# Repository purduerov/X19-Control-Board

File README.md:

# X19 Control Board

Primary microcontroller board managing actuator actuation, telemetry collection, and vehicle subsystem communication for the Purdue ROV X19 vehicle.

---

## 🚀 Quickstart: Opening the Project (Recommended)

**Always open the project using the 1-click launcher:**

* **Windows:** Double-click `LAUNCH_KICAD.bat`
* **macOS / Linux:** Run `./LAUNCH_KICAD.sh`

### What the Launcher Does Automatically:
1. ⚙️ **Configures Git Hooks & Clean Filters:** Sets up Git to strip volatile viewport/zoom coordinates on every commit, preventing merge conflicts.
2. 🔄 **Auto-Updates Component Library:** Pulls the freshest symbols, footprints, and 3D models from `purdue-rov-kicad-lib` before opening.
3. 📐 **Opens KiCad:** Launches `X19-Control-Board.kicad_pro` with all 6 central library categories pre-linked.

---

## Cloning the Repository
Clone recursively to ensure the central component library is initialized:
```bash
git clone --recursive https://github.com/purduerov/X19-Control-Board.git
cd X19-Control-Board
```

## Central Component Library & Manager GUI

The project links to the central `purdue-rov-kicad-lib` submodule mapped across 6 categories in `sym-lib-table` and `fp-lib-table`:
- `rov_passives`: Resistors, capacitors, inductors, crystals
- `rov_power`: Voltage regulators, buck/boost converters, MOSFETs, diodes
- `rov_logic`: MCUs, logic ICs, op-amps, drivers, level shifters
- `rov_connectors`: Power terminals, XT60, headers, USB, JST connectors
- `rov_sensors`: IMUs, temperature, pressure sensors
- `rov_mech`: Mounting holes, standoffs, test points

### Launching the Library Manager GUI
To browse parts, inspect footprints, edit properties, or add/delete components in the shared library:
- **Windows:** Double-click `libs\purdue-rov-kicad-lib\LIBRARY_MANAGER.bat`
- **macOS / Linux:** Run `./libs/purdue-rov-kicad-lib/LIBRARY_MANAGER.sh`

## Design Rules & Clearances

- Clearance constraints (JLCPCB 4-layer rules) are configured in `X19-Control-Board.kicad_dru`.
- All symbols and footprints must comply with central library guidelines.

## Automated CI/CD & DevOps Preflight Checks

All CI/CD automation and tooling are centralized in [`purduerov/pcb-devops`](https://github.com/purduerov/pcb-devops):
1. **Automated Git Clean Filters:** Configured automatically by `.githooks/pre-commit` to prevent viewport/zoom merge noise.
2. **KiCad Symbol Linting:** Validates mandatory fields (`MPN`, `Manufacturer`, `Category`, `DigiKey`, `Datasheet`, `Temp_Range`) on all library components.
3. **ERC & DRC Validation:** Executes Electrical and Design Rules Checks via KiBot in GitHub Actions.
4. **Artifact Generation:** Automatically exports Schematic PDFs, Board Layout PDFs, and Interactive HTML BOMs on every pull request.

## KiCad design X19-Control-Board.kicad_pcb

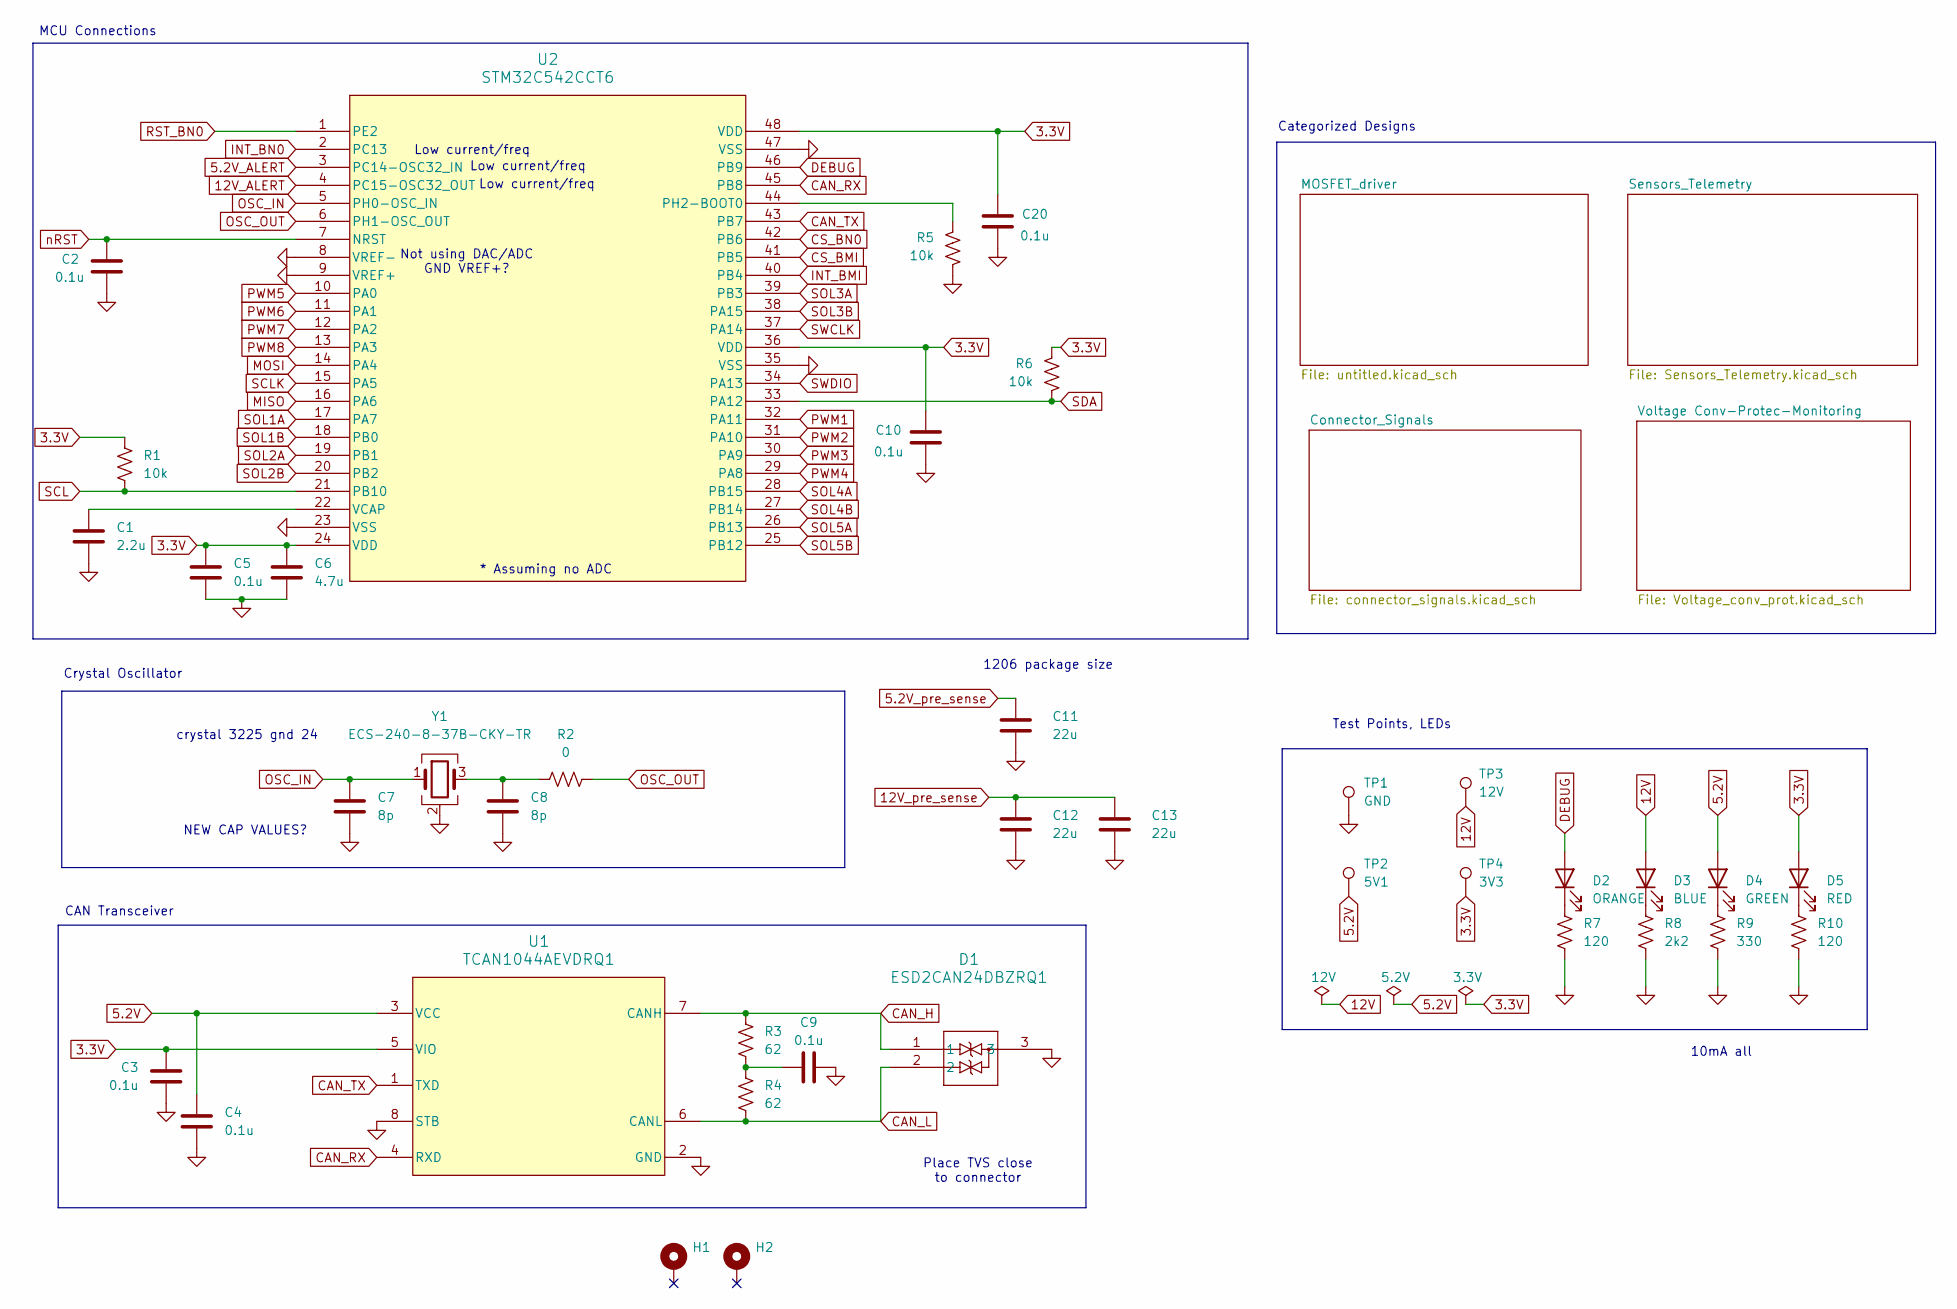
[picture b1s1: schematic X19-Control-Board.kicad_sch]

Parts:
C1: 2.2u; C_0603_1608Metric_Pad1.08x0.95mm_HandSolder; Part Number CC0603KRX5R6BB225
C2, C3, C4, C5, C9, C10, C20: 0.1u; C_0603_1608Metric_Pad1.08x0.95mm_HandSolder; Part Number CC0603KRX7R8BB104
C6: 4.7u; C_0603_1608Metric_Pad1.08x0.95mm_HandSolder; Part Number CC0603KRX5R6BB475
C7, C8: 8p; C_0603_1608Metric_Pad1.08x0.95mm_HandSolder; Part Number CC0603DRNPO9BN8R0
C11, C12, C13: 22u; C_1206_3216Metric_Pad1.33x1.80mm_HandSolder; Part Number CC1206KKX5R8BB226
D1: ESD2CAN24DBZRQ1; SOT-23-3; Part Number ESD2CAN24DBZRQ1
D2: ORANGE; LED_0603_1608Metric; Part Number LTST-C190AKT
D3: BLUE; LED_0603_1608Metric; Part Number LTST-C190TBKT
D4: GREEN; LED_0603_1608Metric; Part Number LTST-C190GKT
D5: RED; LED_0603_1608Metric; Part Number LTST-C190KRKT
H1, H2: MountingHole_Pad; MountingHole_2.7mm_M2.5_Pad
R1, R5, R6: 10k; R_0603_1608Metric_Pad0.98x0.95mm_HandSolder; Part Number RC0603FR-0710KL
R2: 0; R_0603_1608Metric_Pad0.98x0.95mm_HandSolder; Part Number RC0603FR-070RL
R3, R4: 62; R_0603_1608Metric_Pad0.98x0.95mm_HandSolder; Part Number RC0603FR-0762RL
R7, R10: 120; R_0603_1608Metric_Pad0.98x0.95mm_HandSolder; Part Number RC0603FR-07120RL
R8: 2k2; R_0603_1608Metric_Pad0.98x0.95mm_HandSolder; Part Number RC0603FR-072K2L
R9: 330; R_0603_1608Metric_Pad0.98x0.95mm_HandSolder; Part Number RC0603FR-07330RL
TP1: GND; TestPoint_Pad_D1.5mm
TP2: 5V1; TestPoint_Pad_D1.5mm
TP3: 12V; TestPoint_Pad_D1.5mm
TP4: 3V3; TestPoint_Pad_D1.5mm
U1: TCAN1044AEVDRQ1; SOIC-8_3.9x4.9mm_P1.27mm; Part Number TCAN1044AEVDRQ1
U2: STM32C542CCT6; LQFP-48_7x7mm_P0.5mm; Part Number STM32C542CCT6
Y1: ECS-240-8-37B-CKY-TR; Crystal_SMD_2016-4Pin_2.0x1.6mm; Part Number ECS-240-8-37B-CKY-TR

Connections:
3.3V: C3.1, C5.1, C6.1, C10.2, C20.2, D5.2 (A), R1.1, R6.1, TP4.1 (1_1), U1.5 (VIO), U2.24 (VDD), U2.36 (VDD), U2.48 (VDD); also elsewhere on the board
5.2V: C4.1, D4.2 (A), TP2.1 (1_1), U1.3 (VCC); also elsewhere on the board
5.2V_ALERT: U2.3 (PC14-OSC32_IN); also elsewhere on the board
5.2V_pre_sense: C11.1; also elsewhere on the board
12V: D3.2 (A), TP3.1 (1_1); also elsewhere on the board
12V_ALERT: U2.4 (PC15-OSC32_OUT); also elsewhere on the board
12V_pre_sense: C12.1, C13.1; also elsewhere on the board
CAN_H: D1.1, R3.1, U1.7 (CANH); also elsewhere on the board
CAN_L: D1.2, R4.2, U1.6 (CANL); also elsewhere on the board
CAN_RX: U1.4 (RXD), U2.45 (PB8)
CAN_TX: U1.1 (TXD), U2.43 (PB7)
CS_BMI: U2.41 (PB5); also elsewhere on the board
CS_BN0: U2.42 (PB6); also elsewhere on the board
DEBUG: D2.2 (A), U2.46 (PB9)
GND: C1.2, C2.1, C3.2, C4.2, C5.2, C6.2, C7.2, C8.2, C9.2, C10.1, C11.2, C12.2, C13.2, C20.1, D1.3, R5.2, R7.2, R8.2, R9.2, R10.2, TP1.1 (1_1), U1.2 (GND), U1.8 (STB), U2.8 (VREF-), U2.9 (VREF+), U2.23 (VSS), U2.35 (VSS), U2.47 (VSS), Y1.2 (G), Y1.4 (G); also elsewhere on the board
INT_BMI: U2.40 (PB4); also elsewhere on the board
INT_BN0: U2.2 (PC13); also elsewhere on the board
MISO: U2.16 (PA6); also elsewhere on the board
MOSI: U2.14 (PA4); also elsewhere on the board
unnamed: C8.1, R2.1, Y1.3
unnamed: C9.1, R3.2, R4.1
unnamed: D2.1 (K), R7.1
unnamed: D3.1 (K), R8.1
unnamed: D4.1 (K), R9.1
unnamed: D5.1 (K), R10.1
unnamed: R5.1, U2.44 (PH2-BOOT0)
unnamed: C1.1, U2.22 (VCAP)
OSC_IN: C7.1, U2.5 (PH0-OSC_IN), Y1.1
OSC_OUT: R2.2, U2.6 (PH1-OSC_OUT)
PWM1: U2.32 (PA11); also elsewhere on the board
PWM2: U2.31 (PA10); also elsewhere on the board
PWM3: U2.30 (PA9); also elsewhere on the board
PWM4: U2.29 (PA8); also elsewhere on the board
PWM5: U2.10 (PA0); also elsewhere on the board
PWM6: U2.11 (PA1); also elsewhere on the board
PWM7: U2.12 (PA2); also elsewhere on the board
PWM8: U2.13 (PA3); also elsewhere on the board
RST_BN0: U2.1 (PE2); also elsewhere on the board
SCL: R1.2, U2.21 (PB10); also elsewhere on the board
SCLK: U2.15 (PA5); also elsewhere on the board
SDA: R6.2, U2.33 (PA12); also elsewhere on the board
SOL1A: U2.17 (PA7); also elsewhere on the board
SOL1B: U2.18 (PB0); also elsewhere on the board
SOL2A: U2.19 (PB1); also elsewhere on the board
SOL2B: U2.20 (PB2); also elsewhere on the board
SOL3A: U2.39 (PB3); also elsewhere on the board
SOL3B: U2.38 (PA15); also elsewhere on the board
SOL4A: U2.28 (PB15); also elsewhere on the board
SOL4B: U2.27 (PB14); also elsewhere on the board
SOL5A: U2.26 (PB13); also elsewhere on the board
SOL5B: U2.25 (PB12); also elsewhere on the board
SWCLK: U2.37 (PA14); also elsewhere on the board
SWDIO: U2.34 (PA13); also elsewhere on the board
nRST: C2.2, U2.7 (NRST); also elsewhere on the board

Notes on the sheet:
Test Points, LEDs
Low current/freq
CAN Transceiver
* Assuming no ADC
1206 package size
Crystal Oscillator
Not using DAC/ADC GND VREF+?
NEW CAP VALUES?
MCU Connections
10mA all
crystal 3225 gnd 24
Place TVS close to connector
Categorized Designs

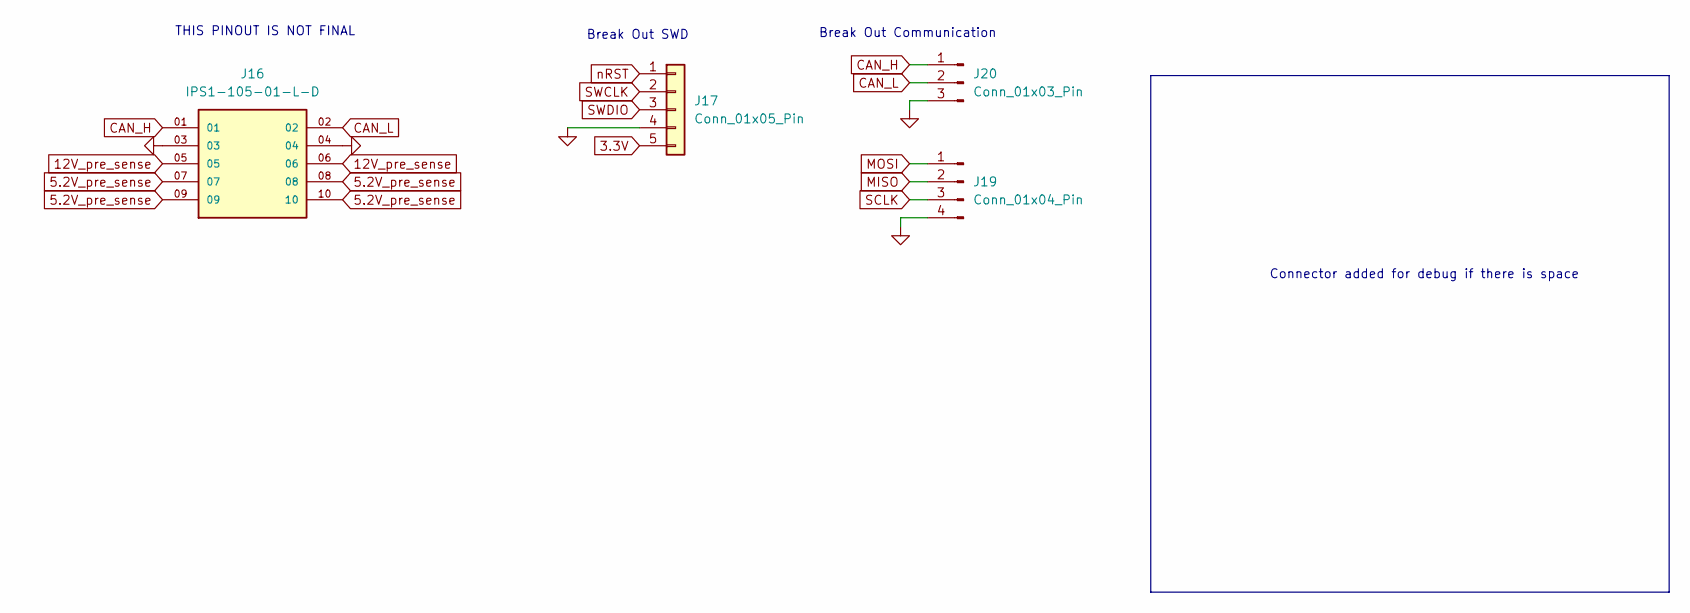
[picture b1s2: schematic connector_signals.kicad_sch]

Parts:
J16: IPS1-105-01-L-D; SAMTEC_IPS1-105-01-S-D; PARTREV R
J17: Conn_01x05_Pin; PinHeader_1x05_P2.54mm_Vertical; Part Number Generic
J19: Conn_01x04_Pin; PinHeader_1x04_P2.54mm_Vertical; Part Number Generic
J20: Conn_01x03_Pin; PinHeader_1x03_P2.54mm_Vertical; Part Number Generic

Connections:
3.3V: J17.5; also elsewhere on the board
5.2V_pre_sense: J16.07, J16.08, J16.09, J16.10; also elsewhere on the board
12V_pre_sense: J16.05, J16.06; also elsewhere on the board
CAN_H: J16.01, J20.1; also elsewhere on the board
CAN_L: J16.02, J20.2; also elsewhere on the board
GND: J16.03, J16.04, J17.4, J19.4, J20.3; also elsewhere on the board
MISO: J19.2; also elsewhere on the board
MOSI: J19.1; also elsewhere on the board
SCLK: J19.3; also elsewhere on the board
SWCLK: J17.2; also elsewhere on the board
SWDIO: J17.3; also elsewhere on the board
nRST: J17.1; also elsewhere on the board

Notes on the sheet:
Break Out Communication
Connector added for debug if there is space
THIS PINOUT IS NOT FINAL
Break Out SWD

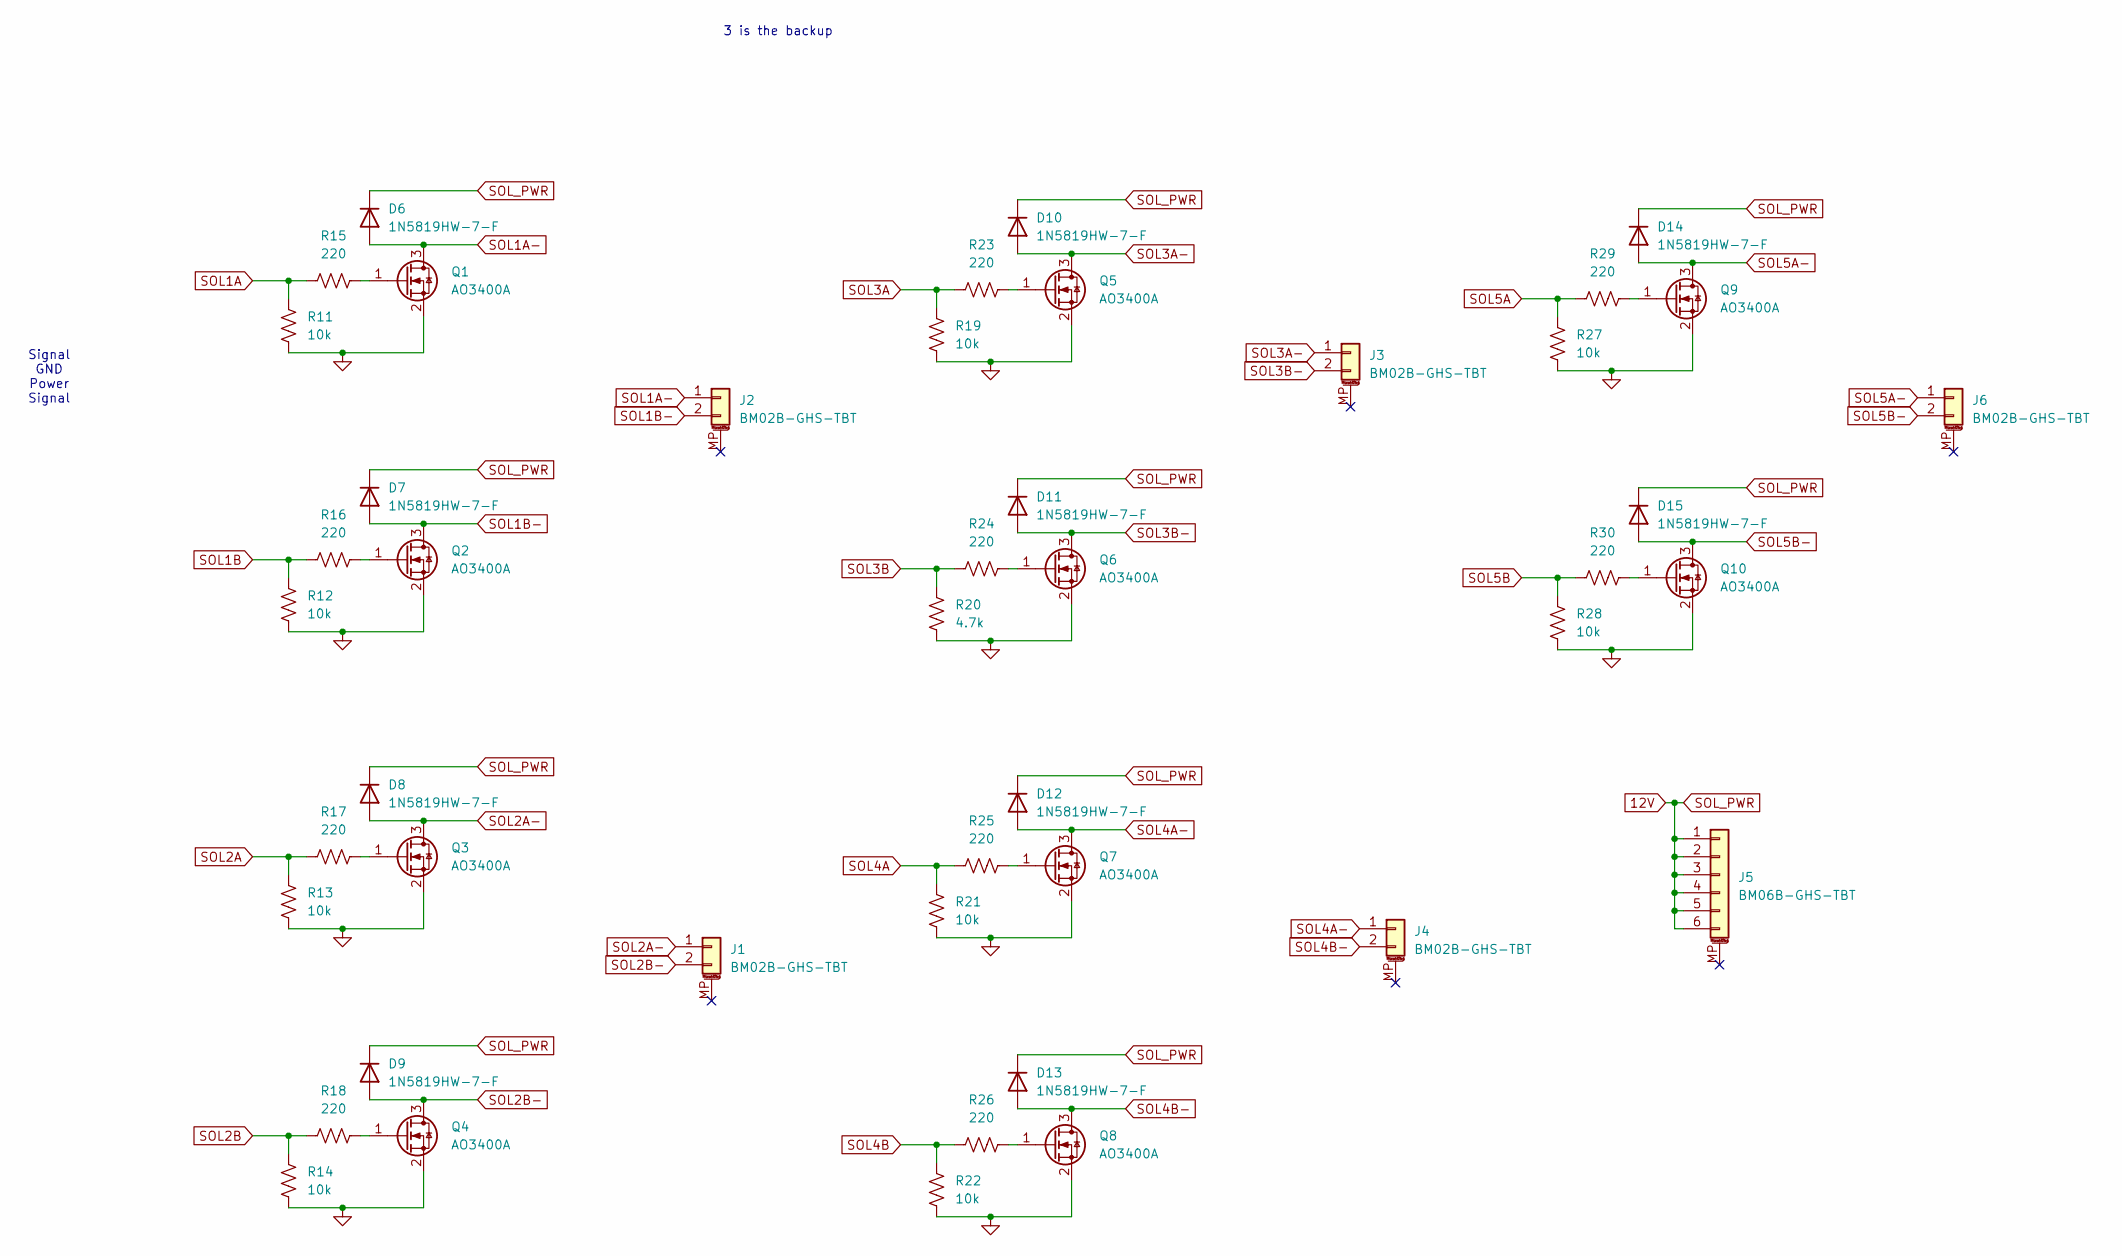
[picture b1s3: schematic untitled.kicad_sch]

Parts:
D6, D7, D8, D9, D10, D11, D12, D13, D14, D15: 1N5819HW-7-F; D_SOD-123; Part Number 1N5819HW-7-F
J1, J2, J3, J4, J6: BM02B-GHS-TBT; JST_GH_BM02B-GHS-TBT_1x02-1MP_P1.25mm_Vertical; Part Number BM02B-GHS-TBT
J5: BM06B-GHS-TBT; JST_GH_BM06B-GHS-TBT_1x06-1MP_P1.25mm_Vertical; Part Number BM06B-GHS-TBT
Q1, Q2, Q3, Q4, Q5, Q6, Q7, Q8, Q9, Q10: AO3400A; SOT-23-3; Part Number AO3400A
R11, R12, R13, R14, R19, R21, R22, R27, R28: 10k; R_0603_1608Metric_Pad0.98x0.95mm_HandSolder; Part Number RC0603FR-0710KL
R15, R16, R17, R18, R23, R24, R25, R26, R29, R30: 220; R_0603_1608Metric_Pad0.98x0.95mm_HandSolder; Part Number RC0603FR-07220RL
R20: 4.7k; R_0603_1608Metric_Pad0.98x0.95mm_HandSolder; Part Number RC0603FR-074K7L

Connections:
12V: D6.1 (K), D7.1 (K), D8.1 (K), D9.1 (K), D10.1 (K), D11.1 (K), D12.1 (K), D13.1 (K), D14.1 (K), D15.1 (K), J5.1, J5.2, J5.3, J5.4, J5.5, J5.6; also elsewhere on the board
GND: Q1.2 (S), Q2.2 (S), Q3.2 (S), Q4.2 (S), Q5.2 (S), Q6.2 (S), Q7.2 (S), Q8.2 (S), Q9.2 (S), Q10.2 (S), R11.2, R12.2, R13.2, R14.2, R19.2, R20.2, R21.2, R22.2, R27.2, R28.2; also elsewhere on the board
unnamed: Q1.1 (G), R15.2
unnamed: Q2.1 (G), R16.2
unnamed: Q3.1 (G), R17.2
unnamed: Q4.1 (G), R18.2
unnamed: Q5.1 (G), R23.2
unnamed: Q6.1 (G), R24.2
unnamed: Q7.1 (G), R25.2
unnamed: Q8.1 (G), R26.2
unnamed: Q9.1 (G), R29.2
unnamed: Q10.1 (G), R30.2
SOL1A: R11.1, R15.1; also elsewhere on the board
SOL1A-: D6.2 (A), J2.1, Q1.3 (D)
SOL1B: R12.1, R16.1; also elsewhere on the board
SOL1B-: D7.2 (A), J2.2, Q2.3 (D)
SOL2A: R13.1, R17.1; also elsewhere on the board
SOL2A-: D8.2 (A), J1.1, Q3.3 (D)
SOL2B: R14.1, R18.1; also elsewhere on the board
SOL2B-: D9.2 (A), J1.2, Q4.3 (D)
SOL3A: R19.1, R23.1; also elsewhere on the board
SOL3A-: D10.2 (A), J3.1, Q5.3 (D)
SOL3B: R20.1, R24.1; also elsewhere on the board
SOL3B-: D11.2 (A), J3.2, Q6.3 (D)
SOL4A: R21.1, R25.1; also elsewhere on the board
SOL4A-: D12.2 (A), J4.1, Q7.3 (D)
SOL4B: R22.1, R26.1; also elsewhere on the board
SOL4B-: D13.2 (A), J4.2, Q8.3 (D)
SOL5A: R27.1, R29.1; also elsewhere on the board
SOL5A-: D14.2 (A), J6.1, Q9.3 (D)
SOL5B: R28.1, R30.1; also elsewhere on the board
SOL5B-: D15.2 (A), J6.2, Q10.3 (D)

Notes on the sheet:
3 is the backup
Signal GND Power Signal

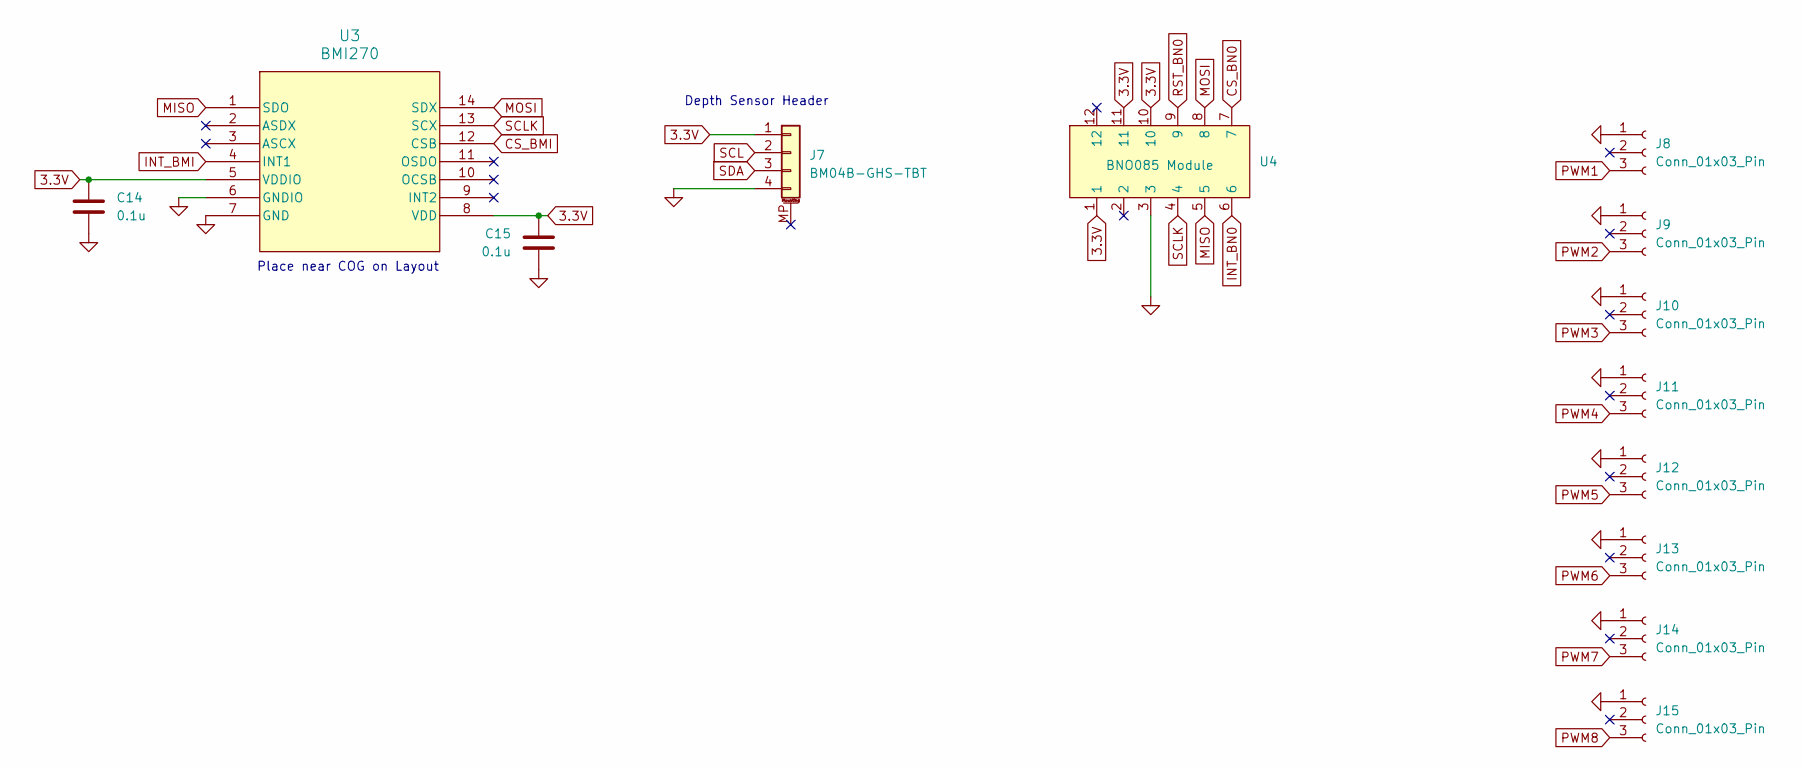
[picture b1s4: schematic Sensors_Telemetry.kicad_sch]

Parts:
C14, C15: 0.1u; C_0603_1608Metric_Pad1.08x0.95mm_HandSolder; Part Number CC0603KRX7R8BB104
J7: BM04B-GHS-TBT; JST_GH_BM04B-GHS-TBT_1x04-1MP_P1.25mm_Vertical; Part Number BM04B-GHS-TBT
J8, J9, J10, J11, J12, J13, J14, J15: Conn_01x03_Pin; PinHeader_1x03_P2.54mm_Vertical; Part Number Generic
U3: BMI270; LGA-14_3x2.5mm_P0.5mm_LayoutBorder3x4y; Part Number BMI270
U4: BNO085 Module; MODULE_4754; Part Number BNO085 Module

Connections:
3.3V: C14.1, C15.1, J7.1, U3.5 (VDDIO), U3.8 (VDD), U4.1, U4.10, U4.11; also elsewhere on the board
CS_BMI: U3.12 (CSB); also elsewhere on the board
CS_BN0: U4.7; also elsewhere on the board
GND: C14.2, C15.2, J7.4, J8.1, J9.1, J10.1, J11.1, J12.1, J13.1, J14.1, J15.1, U3.6 (GNDIO), U3.7 (GND), U4.3; also elsewhere on the board
INT_BMI: U3.4 (INT1); also elsewhere on the board
INT_BN0: U4.6; also elsewhere on the board
MISO: U3.1 (SDO), U4.5; also elsewhere on the board
MOSI: U3.14 (SDX), U4.8; also elsewhere on the board
PWM1: J8.3; also elsewhere on the board
PWM2: J9.3; also elsewhere on the board
PWM3: J10.3; also elsewhere on the board
PWM4: J11.3; also elsewhere on the board
PWM5: J12.3; also elsewhere on the board
PWM6: J13.3; also elsewhere on the board
PWM7: J14.3; also elsewhere on the board
PWM8: J15.3; also elsewhere on the board
RST_BN0: U4.9; also elsewhere on the board
SCL: J7.2; also elsewhere on the board
SCLK: U3.13 (SCX), U4.4; also elsewhere on the board
SDA: J7.3; also elsewhere on the board

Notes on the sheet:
Place near COG on Layout
Depth Sensor Header

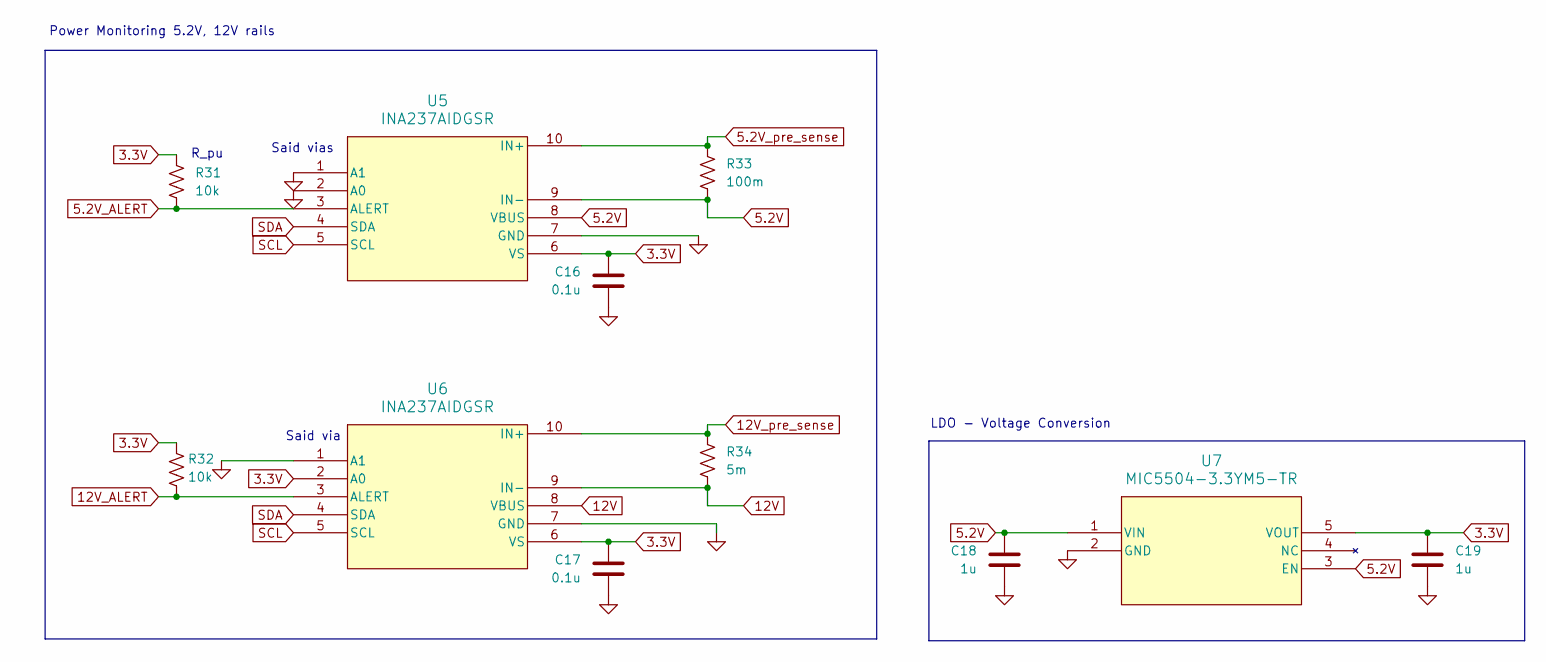
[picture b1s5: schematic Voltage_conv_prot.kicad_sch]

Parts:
C16, C17: 0.1u; C_0603_1608Metric_Pad1.08x0.95mm_HandSolder; Part Number CC0603KRX7R8BB104
C18, C19: 1u; C_0603_1608Metric_Pad1.08x0.95mm_HandSolder; Part Number CC0603KRX5R6BB105
R31, R32: 10k; R_0603_1608Metric_Pad0.98x0.95mm_HandSolder; Part Number RC0603FR-0710KL
R33: 100m; R_0603_1608Metric_Pad0.98x0.95mm_HandSolder; Part Number ERJ-3BWFR100V
R34: 5m; R_0603_1608Metric_Pad0.98x0.95mm_HandSolder; Part Number ERJ-3LWFR005V
U5, U6: INA237AIDGSR; TSSOP-10_3x3mm_P0.5mm; Part Number INA237AIDGSR
U7: MIC5504-3.3YM5-TR; SOT-23-5; Part Number MIC5504-3.3YM5-TR

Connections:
3.3V: C16.1, C17.1, C19.1, R31.1, R32.1, U5.6 (VS), U6.2 (A0), U6.6 (VS), U7.5 (VOUT); also elsewhere on the board
5.2V: C18.1, R33.2, U5.8 (VBUS), U5.9 (IN-), U7.1 (VIN), U7.3 (EN); also elsewhere on the board
5.2V_ALERT: R31.2, U5.3 (ALERT); also elsewhere on the board
5.2V_pre_sense: R33.1, U5.10 (IN+); also elsewhere on the board
12V: R34.2, U6.8 (VBUS), U6.9 (IN-); also elsewhere on the board
12V_ALERT: R32.2, U6.3 (ALERT); also elsewhere on the board
12V_pre_sense: R34.1, U6.10 (IN+); also elsewhere on the board
GND: C16.2, C17.2, C18.2, C19.2, U5.1 (A1), U5.2 (A0), U5.7 (GND), U6.1 (A1), U6.7 (GND), U7.2 (GND); also elsewhere on the board
SCL: U5.5 (SCL), U6.5 (SCL); also elsewhere on the board
SDA: U5.4 (SDA), U6.4 (SDA); also elsewhere on the board

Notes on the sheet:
LDO - Voltage Conversion
Said via
R_pu
Said vias
Power Monitoring 5.2V, 12V rails

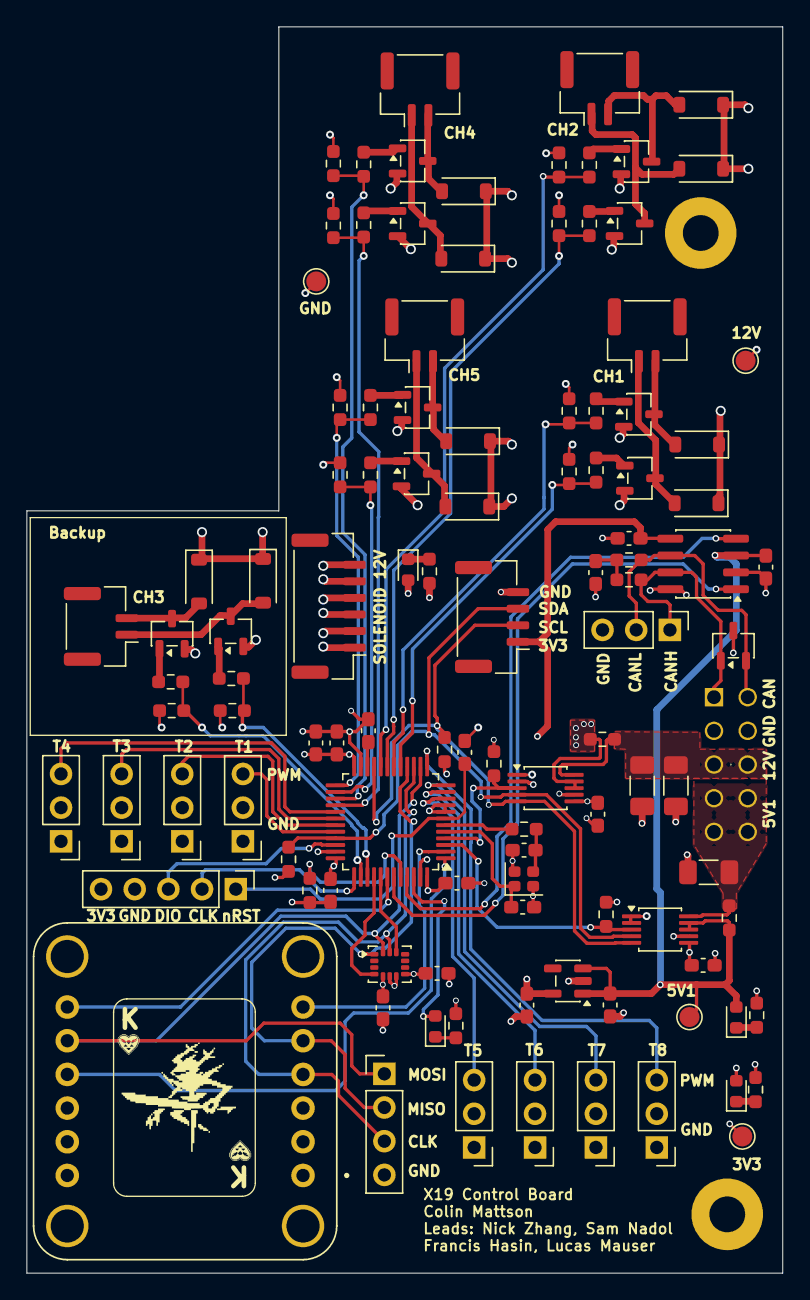
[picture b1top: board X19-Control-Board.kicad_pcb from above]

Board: 4 copper layers, 57.0 x 94.0 mm, 113 parts (1 on the bottom side), 74 nets.

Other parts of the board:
G**: knight_card2

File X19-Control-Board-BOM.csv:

Row,Description,Part,References,Value,Footprint,Quantity Per PCB,Status,Datasheet,Part Number,Sim.Type,KLC_S3.3,KLC_S4.1,Sim.Pins,PARTREV,STANDARD,MANUFACTURER,Sim.Device
1,Unpolarized capacitor,C,C7 C8,8p,C_0603_1608Metric_Pad1.08x0.95mm_HandSolder,2, ,,CC0603DRNPO9BN8R0,,,,,,,,
2,Unpolarized capacitor,C,C2 C3 C4 C5 C9 C10 C14 C15 C16 C17 C20,0.1u,C_0603_1608Metric_Pad1.08x0.95mm_HandSolder,11, ,,CC0603KRX7R8BB104,,,,,,,,
3,Unpolarized capacitor,C,C18 C19,1u,C_0603_1608Metric_Pad1.08x0.95mm_HandSolder,2, ,,CC0603KRX5R6BB105,,,,,,,,
4,Unpolarized capacitor,C,C1,2.2u,C_0603_1608Metric_Pad1.08x0.95mm_HandSolder,1, ,,CC0603KRX5R6BB225,,,,,,,,
5,Unpolarized capacitor,C,C6,4.7u,C_0603_1608Metric_Pad1.08x0.95mm_HandSolder,1, ,,CC0603KRX5R6BB475,,,,,,,,
6,Unpolarized capacitor,C,C11 C12 C13,22u,C_1206_3216Metric_Pad1.33x1.80mm_HandSolder,3, ,,CC1206KKX5R8BB226,,,,,,,,
7,Diode,D,D6 D7 D8 D9 D10 D11 D12 D13 D14 D15,1N5819HW-7-F,D_SOD-123,10, ,,1N5819HW-7-F,,,,1=K 2=A,,,,D
8,Light emitting diode,LED,D3,BLUE,LED_0603_1608Metric,1, ,,LTST-C190TBKT,,,,1=K 2=A,,,,
9,,ESD2CAN24DBZRQ1,D1,ESD2CAN24DBZRQ1,SOT-23-3,1, ,,ESD2CAN24DBZRQ1,,,,,,,,
10,Light emitting diode,LED,D4,GREEN,LED_0603_1608Metric,1, ,,LTST-C190GKT,,,,1=K 2=A,,,,
11,Light emitting diode,LED,D2,ORANGE,LED_0603_1608Metric,1, ,,LTST-C190AKT,,,,1=K 2=A,,,,
12,Light emitting diode,LED,D5,RED,LED_0603_1608Metric,1, ,,LTST-C190KRKT,,,,1=K 2=A,,,,
13,"Generic connectable mounting pin connector, single row, 01x02, script generated (kicad-library-utils/schlib/autogen/connector/)",Conn_01x02_MountingPin,J1 J2 J3 J4 J6,BM02B-GHS-TBT,JST_GH_BM02B-GHS-TBT_1x02-1MP_P1.25mm_Vertical,5, ,,BM02B-GHS-TBT,,,,,,,,
14,"Generic connectable mounting pin connector, single row, 01x04, script generated (kicad-library-utils/schlib/autogen/connector/)",Conn_01x04_MountingPin,J7,BM04B-GHS-TBT,JST_GH_BM04B-GHS-TBT_1x04-1MP_P1.25mm_Vertical,1, ,,BM04B-GHS-TBT,,,,,,,,
15,"Generic connectable mounting pin connector, single row, 01x06, script generated (kicad-library-utils/schlib/autogen/connector/)",Conn_01x06_MountingPin,J5,BM06B-GHS-TBT,JST_GH_BM06B-GHS-TBT_1x06-1MP_P1.25mm_Vertical,1, ,,BM06B-GHS-TBT,,,,,,,,
16,,IPS1-105-01-L-D,J16,IPS1-105-01-L-D,SAMTEC_IPS1-105-01-S-D,1, ,,IPS1-105-01-L-D,,,,,R,Manufacturer Recommendations,Samtec,
17,"N-MOSFET transistor, gate/source/drain",Q_NMOS_GSD,Q1 Q2 Q3 Q4 Q5 Q6 Q7 Q8 Q9 Q10,AO3400A,SOT-23-3,10, ,,AO3400A,,,,,,,,
18,"Resistor, US symbol",R_US,R2,0,R_0603_1608Metric_Pad0.98x0.95mm_HandSolder,1, ,,RC0603FR-070RL,,,,,,,,
19,"Resistor, US symbol",R_US,R34,5m,R_0603_1608Metric_Pad0.98x0.95mm_HandSolder,1, ,,ERJ-3LWFR005V,,,,,,,,
20,"Resistor, US symbol",R_US,R33,100m,R_0603_1608Metric_Pad0.98x0.95mm_HandSolder,1, ,,ERJ-3BWFR100V,,,,,,,,
21,"Resistor, US symbol",R_US,R3 R4,62,R_0603_1608Metric_Pad0.98x0.95mm_HandSolder,2, ,,RC0603FR-0762RL,,,,,,,,
22,"Resistor, US symbol",R_US,R7 R10,120,R_0603_1608Metric_Pad0.98x0.95mm_HandSolder,2, ,,RC0603FR-07120RL,,,,,,,,
23,"Resistor, US symbol",R_US,R15 R16 R17 R18 R23 R24 R25 R26 R29 R30,220,R_0603_1608Metric_Pad0.98x0.95mm_HandSolder,10, ,,RC0603FR-07220RL,,,,,,,,
24,"Resistor, US symbol",R_US,R9,330,R_0603_1608Metric_Pad0.98x0.95mm_HandSolder,1, ,,RC0603FR-07330RL,,,,,,,,
25,"Resistor, US symbol",R_US,R8,1k,R_0603_1608Metric_Pad0.98x0.95mm_HandSolder,1, ,,RC0603FR-071KL,,,,,,,,
26,"Resistor, US symbol",R_US,R20,4.7k,R_0603_1608Metric_Pad0.98x0.95mm_HandSolder,1, ,,RC0603FR-074K7L,,,,,,,,
27,"Resistor, US symbol",R_US,R1 R5 R6 R11 R12 R13 R14 R19 R21 R22 R27 R28 R31 R32,10k,R_0603_1608Metric_Pad0.98x0.95mm_HandSolder,14, ,,RC0603FR-0710KL,,,,,,,,
28,,BMI270,U3,BMI270,LGA-14_3x2.5mm_P0.5mm_LayoutBorder3x4y,1, ,BMI270,BMI270,,,,,,,,
29,,INA237AIDGSR,U5 U6,INA237AIDGSR,TSSOP-10_3x3mm_P0.5mm,2, ,https://www.ti.com/lit/gpn/ina237,INA237AIDGSR,,,,,,,,
30,,MIC5504-3.3YM5-TR,U7,MIC5504-3.3YM5-TR,SOT-23-5,1, ,MIC5504-3.3YM5-TR,MIC5504-3.3YM5-TR,,,,,,,,
31,,STM32C542CCT6,U2,STM32C542CCT6,LQFP-48_7x7mm_P0.5mm,1, ,https://www.st.com/resource/en/datasheet/stm32c542cc.pdf,STM32C542CCT6,,,,,,,,
32,,TCAN1044VDRQ1,U1,TCAN1044AEVDRQ1,SOIC-8_3.9x4.9mm_P1.27mm,1, ,https://www.ti.com/lit/gpn/tcan1044-q1,TCAN1044AEVDRQ1,,,,,,,,
33,"Four pin crystal, GND on pins 2 and 4",Crystal_GND24,Y1,ECS-240-8-37B-CKY-TR,Crystal_SMD_2016-4Pin_2.0x1.6mm,1, ,,ECS-240-8-37B-CKY-TR,,The rectangle is not a symbol body but a graphical element,Some pins are on 50mil grid to make the symbol small,,,,,





Project info:
Schematic:,X19-Control-Board
Variant:,default
Revision:,
Date:,2026-11-19_22-27-14
KiCad Version:,10.0.5-unknown-202607221313~667fa36054~ubuntu25.10.1
Statistics:
Component Groups:,33
Component Count:,94
Fitted Components:,94
Number of PCBs:,1
Total Components:,94
